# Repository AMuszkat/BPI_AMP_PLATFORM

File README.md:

# BPI AMP Platform

![How the platform is developed: a person sets the goal; an orchestrator agent plans the work and splits it between specialist agents working in parallel; every change is tested on two virtual speakers and reviewed, and a failed test or review sends it back to be fixed; a board operations agent deploys it to the real speakers and reports back](docs/images/agents.png)

The BPI AMP Platform is an autonomous, agentic platform for audio streaming, loudspeaker
tuning and digital signal processing (DSP). It is an open hardware and software stack for
building and tuning custom active loudspeakers, and its software is developed, tested and
deployed by a team of AI agents working under the direction of a person.

Each loudspeaker contains a BananaPi BPI-CM4 compute module on two purpose-built boards. The
speaker receives music over the network, applies its own tuning in real time, and drives a
woofer and a tweeter through two MAX98397 class-D amplifiers. Two speakers form a stereo pair,
tuned together from a single desktop application.

## Autonomous development

The platform is built by specialised AI agents, each responsible for one part of the stack:
the audio plugins, the speaker's audio engine, the controller application, the board
software, and the pictures of the project. A person sets the goal and approves the result. An
orchestrator agent plans the work, runs the specialists in parallel, merges their changes and
has a reviewer agent read them; a failed test or a review comment goes back to the agent that made the change. Every change is tested on two virtual speakers running on one
computer before it is published, and again by continuous integration. A board operations agent
installs the result on the real speakers and checks them. Safeguards apply throughout: no
private data enters the repository, nothing reaches the main branch without review, and a lab
lock keeps the agents away from the boards while they are on the bench. The agents, their
rules and their tools are described in [`CLAUDE.md`](CLAUDE.md) and
[`docs/autonomous-development.md`](docs/autonomous-development.md).

## Overview

Music is played as usual, from a computer or a phone; the speakers take care of the rest.

- **Network streaming.** Snapcast streams the music to both speakers in sync. AirPlay is also
  supported, through shairport-sync.
- **Processing in each speaker.** Each speaker processes its own channel. Its audio engine,
  `speakerd`, runs a chain of plugins: a correction filter, a crossover that divides the signal
  between the woofer and the tweeter, and a loudness contour. A speaker keeps playing from the
  settings stored on it, with no network or controller connected.
- **Tuning from a computer.** The controller application works like a familiar plugin host:
  plugins are added, connected and adjusted in their own editors, and both speakers follow
  within milliseconds. The settings are kept on the speakers, not in the application. The
  `ampd` service on the left speaker acts as the hub that keeps the pair in step; the right
  speaker applies what the hub sends. Level meters are read directly from each speaker.
- **Filters from measurements.** A set of Python tools measures each driver and designs the
  crossover and correction filters, which are then built into the plugins.

### Inside a speaker

Each speaker runs a layered stack: the platform's applications and PipeWire in user space,
the Linux audio drivers in the kernel, and the hardware beneath them.

The diagrams on this page are generated from [`docs/diagrams/`](docs/diagrams).

## Software modules

| Module | Purpose | Runs on | Location |
|---|---|---|---|
| Measurement and tuning tools | Measure a speaker's drivers, design its filters and export them for the plugins | the development computer (Python) | [`dsp/python_dsp_tools`](dsp/python_dsp_tools) |
| Audio plugins | `crossover`, `firConv` (correction), `loudness` and `ampScope`. The first three are each built in three variants from one source: **complete**, **control** (the editor only) and **headless** (the signal processing only) | the speakers (headless), the controller (control) | [`dsp/juce_plugins`](dsp/juce_plugins) |
| `speakerd` | The speaker's audio engine: hosts the plugin chain inside PipeWire, from the settings stored on the speaker | each speaker | [`dsp/juce_apps/speakerd`](dsp/juce_apps/speakerd) |
| `ampd` | The speaker's network service: stores and applies its settings; on the left speaker, also the hub of the pair | each speaker | [`firmware/ampd`](firmware/ampd) |
| Controller | The desktop application for tuning the pair through the hub | the listener's computer | [`dsp/juce_apps/controller`](dsp/juce_apps/controller) |
| PipeWire and Snapcast | The speaker's audio server, and the network stream that feeds it | each speaker | [`firmware/pipewire`](firmware/pipewire), [`firmware/snapcast-setup.sh`](firmware/snapcast-setup.sh) |
| Kernel support | Device tree, kernel configuration, and the amplifier and sound-card drivers | each speaker | [`firmware`](firmware) |
| Installers | `setup.sh` installs the audio software of a speaker, one component at a time | the development computer, or the speaker | [`firmware/setup.sh`](firmware/setup.sh) |

The controller, `ampd` and `speakerd` communicate through the protocol described in
[`docs/protocol.md`](docs/protocol.md). The overall design is described in
[`docs/remote-plugin-host.md`](docs/remote-plugin-host.md).

<table>
  <tr valign="top">
    <td width="50%"></td>
    <td width="50%"></td>
  </tr>
  <tr valign="top">
    <td><b>Tuning tool:</b> driver responses, the crossover sum and the corrected output, with every filter parameter adjustable live.</td>
    <td><b>The loudness plugin in the controller:</b> the plugin's own editor, acting as a remote control for both speakers.</td>
  </tr>
</table>

## Project status

The first three steps of the roadmap are complete and tested: the plugins in their three
variants, the `speakerd` audio engine, and the controller with the hub. Every test run checks
them against a pair of virtual speakers. On 1 November 2026 the platform was first installed
on a real board, which now starts `speakerd` at boot and plays the music Snapcast streams to it.
Running `ampd` and the controller on real boards is the next stage of that installation. Step 4
of the roadmap (oscilloscope data, a catalogue of the plugins on each speaker, and several
controllers at once) is next. `tools/roadmap.py` reports the current state.

## Hardware

The platform uses two boards joined by a board-to-board connector: a **base board** that
carries the BPI-CM4 module, with a USB-C port and a debug serial port, and a **speaker amp
board** with the two MAX98397 amplifiers, a boost converter for their supply and a 5 V
regulator for the rest of the system. The KiCad projects and their details are in
[`hardware/`](hardware/README.md).

The picture alternates between a render of the KiCad projects
([`hardware/render/`](hardware/README.md#renders)) and a photograph of the boards as built
([`all.jpeg`](all.jpeg)).

## Firmware

The board runs Armbian Linux with this repository's device tree, kernel configuration and
amplifier drivers, and PipeWire as its audio server. `firmware/setup.sh` installs the audio
software of a speaker, either from the development computer or on the board itself. The
bring-up procedure and the installers are described in [`firmware/`](firmware/README.md).

## Development

All development and testing, apart from work on the boards themselves, takes place on a Linux
x86_64 computer with no board attached. Only Podman and git are required: the builds and the
tests run in a development container with the same PipeWire version as the boards.

```sh
git clone --recurse-submodules https://github.com/AMuszkat/bpi_amp_platform
cd bpi_amp_platform
tools/test.sh all          # the complete test suite
tools/test.sh changed      # while working: the checks that cover the files changed
tools/build.sh loudness    # build one plugin or application into build/
tools/container.sh         # open a shell in the development container
```

The first run builds the container image and the JUCE framework, which takes a few minutes.
A focused check then takes between a few seconds and two minutes, and the complete suite about
two minutes. For a board, `tools/build.sh speakerd aarch64` cross-compiles into
`build/aarch64/`, and `firmware/setup.sh --mode target-remote` installs the result. Run
`tools/test.sh all` before installing on a board: nothing enforces it.

The Python measurement and tuning tools have their own quick start in
[`dsp/README.md`](dsp/README.md). The development process, including the test levels, the
development agents and continuous integration, is described in [`CLAUDE.md`](CLAUDE.md) and
[`docs/autonomous-development.md`](docs/autonomous-development.md).

## Repository layout

| Directory | Contents |
|---|---|
| [`hardware`](hardware/README.md) | KiCad projects: the base board and the amplifier board |
| [`firmware`](firmware/README.md) | Device tree, kernel configuration, amplifier drivers, PipeWire configuration, the installers and `ampd` |
| [`dsp`](dsp/README.md) | Measurement and tuning tools, the JUCE plugins, `speakerd`, the controller and the plugin test tool |
| [`docs`](docs) | The [system design](docs/remote-plugin-host.md), its [protocol](docs/protocol.md), the [block FIR filter](docs/p1-block-fir.md), the [development setup](docs/autonomous-development.md) and the [diagrams](docs/diagrams) |
| [`tests/vpair`](tests/vpair/README.md) | Two virtual speakers on one computer, for development and testing without boards |
| [`tools`](tools) | Build, test, container and board scripts |

## License

The software under [`dsp/`](dsp) is free software, licensed under the GNU Affero General Public
License v3.0; see [`dsp/LICENSE`](dsp/LICENSE).

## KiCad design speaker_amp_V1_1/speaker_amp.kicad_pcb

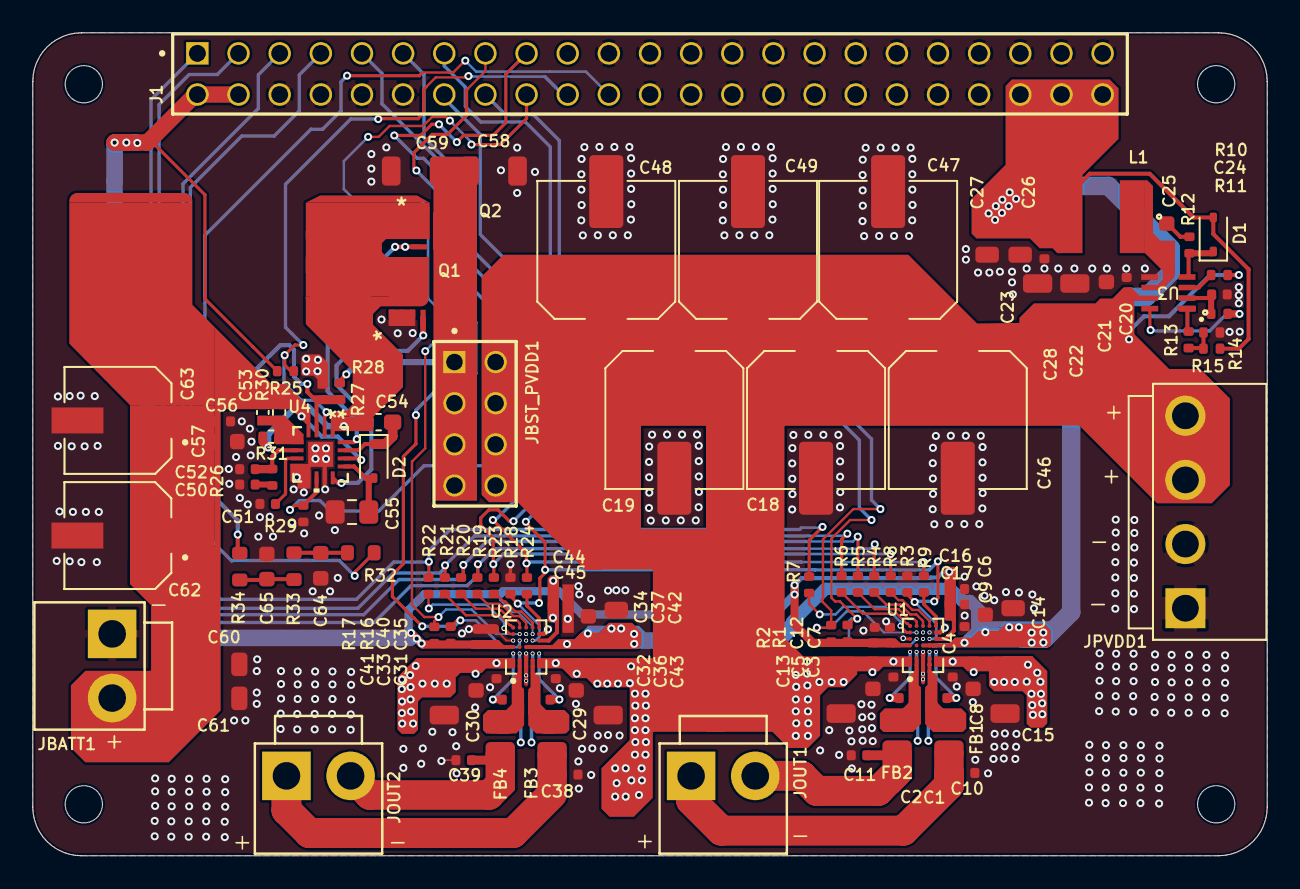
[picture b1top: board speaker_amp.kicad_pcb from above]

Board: 4 copper layers, 76.2 x 50.8 mm, 119 parts (0 on the bottom side), 65 nets.

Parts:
C1, C2, C3, C4, C6, C7, C16, C20, C24, C28, C29, C30, C31, C32, C34, C35, C44, C50, C51, C52, C56: 100nF; C_0402_1005Metric
C5, C8, C9, C21, C25, C33, C36, C37, C57, C64, C65: 1uF; C_0603_1608Metric
C10, C11, C38, C39: 150pF; C_0402_1005Metric
C12, C17, C40, C45: 1uF; C_0402_1005Metric
C13, C15, C22, C23, C41, C43, C58, C59: 10uF; C_1206_3216Metric
C14, C26, C27, C42: 22uF; C_0805_2012Metric
C18, C19, C46, C47, C48, C49: 470uF; C_ELEC_8x10
C53: 0.047uF; C_0402_1005Metric
C54: 1uF; C_0603_1608Metric_Pad1.08x0.95mm_HandSolder
C55: 4.7uF; C_0805_2012Metric_Pad1.18x1.45mm_HandSolder
C60, C61: 10uF; C_0805_2012Metric
C62, C63: 47uF; CAP_EEEFK1C470P
D1, D2: 1N4148WS; D_SOD-323
FB1, FB2, FB3, FB4: FERR_NFZ2MSD301SZ10L; NFZ2MSD301SZ10L
J1: CONN_2x23PIN; SAMTEC_SSW-123-01-T-D
JBATT1: Conn_01x02; B2P-VH
JBST_PVDD1: Conn_02x04_Odd_Even; TSW-104-07-F-D
JOUT1, JOUT2: Conn_01x02; B2P-VH
JPVDD1: Conn_01x04; B4P-VH
L1: L_74404054xx; IND_5040-WE-LQS_WRE
L2: 4.7uH; HCM1A1307-4R7-R
Q1, Q2: BSZ024N04LS6; PQFN330x330
R1, R3, R10, R11, R16, R18, R25, R26, R27, R28, R29: 10K; R_0402_1005Metric
R2, R12, R17: 4.7k; R_0402_1005Metric
R4, R5, R6, R7, R8, R9, R19, R20, R21, R22, R23, R24: 33r; R_0402_1005Metric
R13: 51K; R_0402_1005Metric
R14: 7.68K; R_0402_1005Metric
R15: 41.2K; R_0402_1005Metric
R30: 10M; R_0402_1005Metric
R31: 13.3K; R_0402_1005Metric
R32, R33, R34: R_0603_1608Metric
U1, U2: WLP35
U3: MP9943; QFN-8_MP9943_MNP
U4: LTC3786; QFN-16_UD_LIT

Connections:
+1V8: C7.1, C12.1, C16.1, C17.1, C35.1, C40.1, C44.1, C45.1, J1.2, J1.4, R1.1, R2.1, R16.1, R17.1, R25.1, U1.A4 (AVDD), U1.E5 (DVDD), U2.A4 (AVDD), U2.D6 (ADDR1), U2.E5 (DVDD)
+5V: C6.1, C9.1, C14.1, C26.1, C27.1, C28.1, C34.1, C37.1, C42.1, D1.2 (A), J1.42, J1.44, J1.46, L1.2, R15.1, U1.C4 (VBAT), U1.D4 (VBAT), U1.E4 (VBAT), U2.C4 (VBAT), U2.D4 (VBAT), U2.E4 (VBAT)
/Amp1/OUTN: C2.1, FB2.1, U1.B1 (OUTN), U1.B2 (OUTN)
/Amp1/OUTNSN: C11.1, FB2.2, JOUT1.2, U1.B3 (OUTNSNS)
/Amp1/OUTP: C1.2, FB1.1, U1.D1 (OUTP), U1.D2 (OUTP)
/Amp1/OUTPSN: C10.1, FB1.2, JOUT1.1, U1.D3 (OUTPSNS)
/Amp1/VBOOTN: C2.2, U1.A3 (VBOOTN)
/Amp1/VBOOTP: C1.1, U1.E3 (VBOOTP)
/Amp2/OUTN: C30.1, FB4.1, U2.B1 (OUTN), U2.B2 (OUTN)
/Amp2/OUTNSN: C39.1, FB4.2, JOUT2.2, U2.B3 (OUTNSNS)
/Amp2/OUTP: C29.2, FB3.1, U2.D1 (OUTP), U2.D2 (OUTP)
/Amp2/OUTPSN: C38.1, FB3.2, JOUT2.1, U2.D3 (OUTPSNS)
/Amp2/VBOOTN: C30.2, U2.A3 (VBOOTN)
/Amp2/VBOOTP: C29.1, U2.E3 (VBOOTP)
/Boost/OUT_FB: C58.1, C59.1, JBST_PVDD1.1, JBST_PVDD1.3, JBST_PVDD1.5, JBST_PVDD1.7, Q2.5 (D), R27.1
/Buck5V/PGOOD: R11.2, U3.8 (PG)
/GPIOA_1: J1.14, R3.1, R18.1, U1.D5 (/RESET), U2.D5 (/RESET)
/GPIOA_2: J1.13, R1.2, U1.B5 (IRQ)
/GPIOA_3: J1.16, R2.2, U1.B6 (LV_EN)
/GPIOA_4: J1.15, R16.2, U2.B5 (IRQ)
/GPIOA_5: J1.18, R17.2, U2.B6 (LV_EN)
/GPIOA_6: J1.17, R29.2, U4.10 (RUN)
/GPIOA_7: J1.20, R25.2, U4.2 (PGOOD)
/GPIOA_9: J1.22, R32.2
/I2C_EE_M2_SCL: J1.9, R9.1, R24.1
/I2C_EE_M2_SDA: J1.11, R8.1, R23.1
/ICC_AMP: U1.C6 (ICC), U2.C6 (ICC)
/TDMA_D0: J1.5, R6.1, R21.1
/TDMA_D1: J1.7, R7.1, R22.1
/TDMA_FS: J1.3, R5.1, R20.1
/TDMA_SCLK: J1.1, R4.1, R19.1
GND: C3.2, C4.2, C5.2, C6.2, C7.2, C8.2, C9.2, C10.2, C11.2, C12.2, C13.2, C14.2, C15.2, C16.2, C17.2, C18.2, C19.2, C20.2, C21.2, C22.2, C23.2, C24.2, C26.2, C27.2, C28.2, C31.2, C32.2, C33.2, C34.2, C35.2, C36.2, C37.2, C38.2, C39.2, C40.2, C41.2, C42.2, C43.2, C44.2, C45.2, C46.2, C47.2, C48.2, C49.2, C50.1, C51.1, C52.1, C55.2, C56.2, C57.2, C58.2, C59.2, C60.2, C61.2, C62.2, C63.2, C64.2, C65.2, J1.6, J1.8, J1.10, J1.12, J1.21, J1.23, J1.24, J1.25, J1.26, J1.27, J1.28, J1.29, J1.30, J1.31, J1.32, J1.33, J1.34, J1.35, J1.36, J1.37, J1.38, J1.39, J1.40, J1.41, J1.43, J1.45, JBATT1.1, JPVDD1.1, JPVDD1.2, Q1.1 (S), Q1.2 (S), Q1.3 (S), R3.2, R14.2, R18.2, R28.2, R29.1, U1.A5 (AGND), U1.C1 (PGND), U1.C2 (PGND), U1.C3 (PGND), U1.C5 (ADDR2), U1.D6 (ADDR1), U1.E6 (DGND), U2.A5 (AGND), U2.C1 (PGND), U2.C2 (PGND), U2.C3 (PGND), U2.C5 (ADDR2), U2.E6 (DGND), U3.5 (GND), U4.8 (PLLIN/MODE), U4.9 (FREQ), U4.11 (GND), U4.17 (EPAD)
unnamed: C25.1, R12.2
unnamed: C50.2, R26.2
unnamed: C64.1, R32.1, R33.2
unnamed: C65.1, R33.1, R34.2
unnamed: D1.1 (K), R12.1, U3.4 (BST)
unnamed: C55.1, D2.2 (A), U4.13 (INTVCC)
unnamed: C54.2, D2.1 (K), U4.15 (BOOST)
unnamed: C54.1, L2.2, Q1.5 (D), Q2.1 (S), Q2.2 (S), Q2.3 (S), R31.2, U4.1 (SW)
unnamed: Q1.4 (G), U4.12 (BG)
unnamed: Q2.4 (G), U4.16 (TG)
unnamed: R13.1, R14.1, R15.2
unnamed: R4.2, U1.C7 (BCLK)
unnamed: R6.2, U1.A7 (DIN)
unnamed: R7.2, U1.A6 (DOUT)
unnamed: R5.2, U1.B7 (LRCLK)
unnamed: R9.2, U1.E7 (SCL)
unnamed: R8.2, U1.D7 (SDA)
unnamed: R19.2, U2.C7 (BCLK)
unnamed: R21.2, U2.A7 (DIN)
unnamed: R22.2, U2.A6 (DOUT)
unnamed: R20.2, U2.B7 (LRCLK)
unnamed: R24.2, U2.E7 (SCL)
unnamed: R23.2, U2.D7 (SDA)
unnamed: R10.2, U3.3 (EN/SYNC)
unnamed: R13.2, U3.1 (FB)
unnamed: C25.2, L1.1, U3.6 (SW)
unnamed: C24.1, R11.1, U3.2 (VCC)
unnamed: C52.2, R26.1, U4.6 (ITH)
unnamed: C53.2, R30.2, R31.1, U4.5 (SENSE-)
unnamed: C51.2, U4.7 (SS)
unnamed: R27.2, R28.1, R34.1, U4.3 (VFB)
PVDD: C3.1, C4.1, C5.1, C8.1, C13.1, C15.1, C18.1, C19.1, C20.1, C21.1, C22.1, C23.1, C31.1, C32.1, C33.1, C36.1, C41.1, C43.1, C46.1, C47.1, C48.1, C49.1, JBST_PVDD1.2, JBST_PVDD1.4, JBST_PVDD1.6, JBST_PVDD1.8, JPVDD1.3, JPVDD1.4, R10.1, U1.A1 (PVDD), U1.A2 (PVDD), U1.E1 (PVDD), U1.E2 (PVDD), U2.A1 (PVDD), U2.A2 (PVDD), U2.E1 (PVDD), U2.E2 (PVDD), U3.7 (IN)
VBATT_EXT: C53.1, C56.1, C57.1, C60.1, C61.1, C62.1, C63.1, JBATT1.2, L2.1, R30.1, U4.4 (SENSE+), U4.14 (VBIAS)

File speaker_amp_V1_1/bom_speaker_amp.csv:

Reference;Description;Value;Qty;Type;Voltage;Footprint size;Tolerance;DNP;MPN;Manufacturer;Critical part (must be same as MPN)
D1,D2;DIODE;1N4148WS;2;;;;;;1N4148WS-E3-18;Vishay Semiconductors;
U4;IC;LTC3786;1;;;;;;LTC3786EUD#TRPBF;Analog Devices;Critical
U3;IC;MP9943;1;;;;;;MP9943AGQ-Z;Monolithic Power Systems (MPS);Critical
U1,U2;;MAX98397;2;;;;;;MAX98397EWB+T;Analog Devices;Critical
R31;RES;13.3K;1;;;0402;1%;;RMCF0402FT13K3;SEI Stackpole;
R30;RES;10M;1;;;0402;1%;;RMCF0402FT10M0;SEI Stackpole;
R15;RES;41.2K;1;;;0402;1%;;RC0402FR-1341K2L;YAGEO;
R14;RES;7.68K;1;;;0402;1%;;RC0402FR-077K68L;YAGEO;
R13;RES;51K;1;;;0402;1%;;RC0402FR-0751KP;YAGEO;
R12;Resistor;4.7k;1;;;0603;1%;;CRCW06034K70FKEC;Vishay / Dale;
R4,R5,R6,R7,R8,R9,R19,R20,R21,R22,R23,R24;RES;33r;12;;;0402;1%;;RC0402FR-1333RL;YAGEO;
R2,R17;RES;4.7k;2;;;0402;1%;;AC0402FR-134K7L;YAGEO;
R1,R3,R10,R11,R16,R18,R25,R26,R27,R28,R29;RES;10K;11;;;0402;1%;;AC0402FR-0710KL;YAGEO;
Q1,Q2;100A Id, 60V Vds, OptiMOS N-Channel Power MOSFET, 2.8mOhm Ron, Qg (typ) 31.0nC, PG-TDSON-8;BSZ024N04LS6;2;;;;;;BSZ024N04LS6;Infineon;Critical
L2;IND;4.7uH;1;;;;;;HCM1A1307-4R7-R;Bussmann / Eaton;Critical
L1;Inductor;10uH;1;;;;;;74404054100;Würth Elektronik;Critical
JPVDD1;CONN;Conn_01x04;1;;;;;DNP;B4P-VH;JST Sales America Inc.;
JBST_PVDD1;HEADER;Conn_02x04_Odd_Even;1;;;;;DNP;TSW-104-07-F-D;Samtec;
JBATT1,JOUT1,JOUT2;CONN;Conn_01x02;3;;;;;DNP;B2P-VH;JST Sales America Inc.;
FB1,FB2,FB3,FB4;FERR;FERR_NFZ2MSD301SZ10L;4;;;0806;;;NFZ2MSD301SZ10L;Murata;Critical
C64,C65,J1,R32,R33,R34;-;-;-;-;-;-;-;DNP;;;
C62,C63;CAP;47uF;2;ELEC;16V;-;10%;DNP;EEE-FK1C470P;Panasonic;
C60,C61;CAP;10uF;2;X7R;25V;0805;20%;;CL21B106KAYQNNE;Samsung Electro-Mechanics;
C55;CAP;4.7uF;1;X7R;25V;0805;10%;;GRM21BZ71E475KE15L;Murata;
C54;CAP;1uF;1;X7R;50V;0603;10%;;GCM188R71E104KA57D;Murata;
C53;CAP;0.047uF;1;X7R;25V;0402;5%;;GRM155R71E473JA88D;Murata;
C18,C19,C46,C47,C48,C49;;470uF;6;ELEC;50V;-;10%;DNP;EMZS350ARA471MHA0G;Chemi-Con;
C14,C26,C27,C42;CAP;22uF;4;X7R;10V;0805;20%;;GRM21BZ71A226ME15K;Murata;
C13,C15,C22,C23,C41,C43,C58,C59;CAP;10uF;8;X7R;50V;1206;10%;;CL31B106KBHNNNE;Samsung Electro-Mechanics;
C12,C17,C40,C45;CAP;1uF;4;X7R;10V;0402;10%;;GRM155Z71A105KE01J;Murata;Critical
C10,C11,C38,C39;CAP;150pF;4;NP0;50V;0402;10%;;UMK105CG151JVHF;TAIYO YUDEN;
C5,C8,C9,C21,C25,C33,C36,C37,C57;CAP;1uF;9;X7R;50V;0603;10%;;CL10B105KB8NQNC;Samsung Electro-Mechanics;
C1,C2,C3,C4,C6,C7,C16,C20,C24,C28,C29,C30,C31,C32,C34,C35,C44,C50,C51,C52,C56;CAP;100nF;21;X7R;50V;0402;10%;;GRM155R71H104KE14D;Murata;

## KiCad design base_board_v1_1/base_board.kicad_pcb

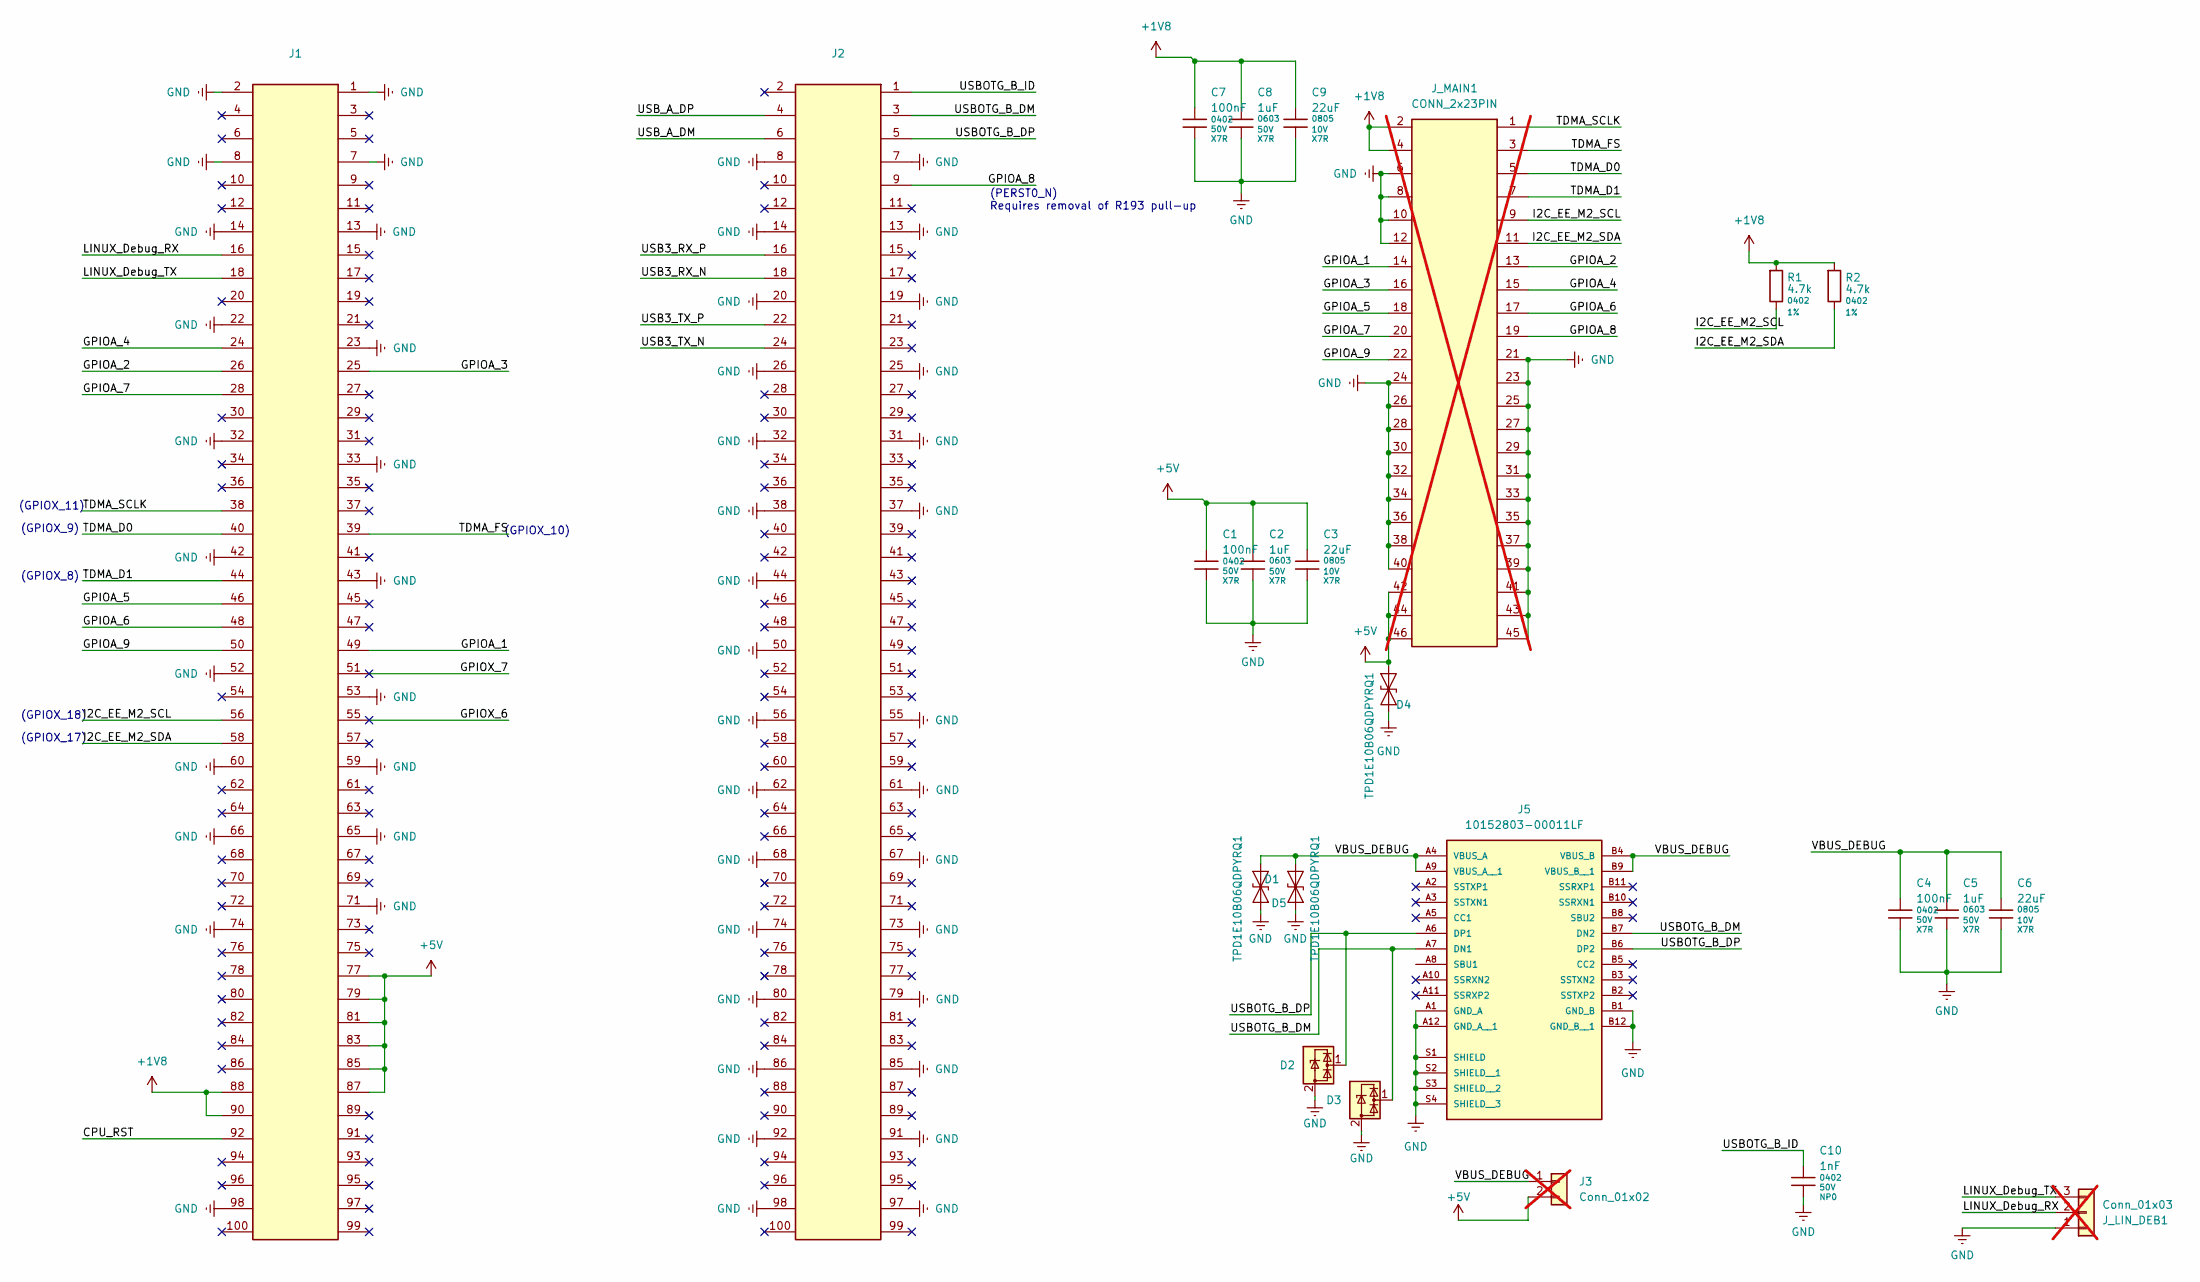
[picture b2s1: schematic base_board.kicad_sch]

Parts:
C1, C4, C7: 100nF; C_0402_1005Metric; Voltage 50V; Tolerance 10%; MPN GRM155R71H104KE14D
C2, C5, C8: 1uF; C_0603_1608Metric; Voltage 50V; Tolerance 10%; MPN CL10B105KB8NQNC
C3, C6, C9: 22uF; C_0805_2012Metric; Voltage 10V; Tolerance 20%; MPN GRM21BZ71A226ME15K
C10: 1nF; C_0402_1005Metric; Voltage 50V; Tolerance 5%; MPN C0402C102J5GAC
D1, D4, D5: SOD-523; MPN TPD1E10B06QDPYRQ1
D2, D3: Texas_DPY0002A_0.6x1mm_P0.65mm; MPN TPD1E1B04
J1: CONN_DF40HC-100DS_HIR_v1_1; MPN DF40HC(3.0)-100DS-0.4V(51
J2: CONN_DF40HC-100DS_HIR_v1_1; MPN DF40HC(3.0)-100DS-0.4V(51
J3: Conn_01x02; PinHeader_2x01_P2.54mm_Vertical; not fitted
J5: 10152803-00011LF; AMPHENOL_10152803-00011LF; PARTREV A
J_LIN_DEB1: Conn_01x03; PinHeader_1x03_P2.54mm_Vertical; not fitted
J_MAIN1: CONN_2x23PIN; SAMTEC_SSW-123-01-T-D; not fitted
R1, R2: 4.7k; R_0402_1005Metric; Tolerance 1%; MPN RCG04024K70FKED

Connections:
+1V8: C7.1, C8.1, C9.1, J1.88, J1.90, J_MAIN1.2, J_MAIN1.4, R1.1, R2.1
+5V: C1.1, C2.1, C3.1, D4.1 (A1), J1.77, J1.79, J1.81, J1.83, J1.85, J1.87, J3.2, J_MAIN1.42, J_MAIN1.44, J_MAIN1.46
/CPU_RST: J1.92
/GPIOA_1: J1.49, J_MAIN1.14
/GPIOA_2: J1.26, J_MAIN1.13
/GPIOA_3: J1.25, J_MAIN1.16
/GPIOA_4: J1.24, J_MAIN1.15
/GPIOA_5: J1.46, J_MAIN1.18
/GPIOA_6: J1.48, J_MAIN1.17
/GPIOA_7: J1.28, J_MAIN1.20
/GPIOA_8: J2.9, J_MAIN1.19
/GPIOA_9: J1.50, J_MAIN1.22
/GPIOX_6: J1.55
/GPIOX_7: J1.51
/I2C_EE_M2_SCL: J1.56, J_MAIN1.9, R1.2
/I2C_EE_M2_SDA: J1.58, J_MAIN1.11, R2.2
/LINUX_Debug_RX: J1.16, J_LIN_DEB1.2
/LINUX_Debug_TX: J1.18, J_LIN_DEB1.3
/TDMA_D0: J1.40, J_MAIN1.5
/TDMA_D1: J1.44, J_MAIN1.7
/TDMA_FS: J1.39, J_MAIN1.3
/TDMA_SCLK: J1.38, J_MAIN1.1
/USB3_RX_N: J2.18
/USB3_RX_P: J2.16
/USB3_TX_N: J2.24
/USB3_TX_P: J2.22
/USBOTG_B_DM: D3.1 (I/O), J2.3, J5.A7 (DN1), J5.B7 (DN2)
/USBOTG_B_DP: D2.1 (I/O), J2.5, J5.A6 (DP1), J5.B6 (DP2)
/USBOTG_B_ID: C10.1, J2.1
/USB_A_DM: J2.6
/USB_A_DP: J2.4
/VBUS_DEBUG: C4.1, C5.1, C6.1, D1.1 (A1), D5.1 (A1), J3.1, J5.A4 (VBUS_A), J5.A9 (VBUS_A__1), J5.B4 (VBUS_B), J5.B9 (VBUS_B__1)
GND: C1.2, C2.2, C3.2, C4.2, C5.2, C6.2, C7.2, C8.2, C9.2, C10.2, D1.2 (A2), D2.2 (GND), D3.2 (GND), D4.2 (A2), D5.2 (A2), J1.1, J1.2, J1.7, J1.8, J1.13, J1.14, J1.22, J1.23, J1.32, J1.33, J1.42, J1.43, J1.52, J1.53, J1.59, J1.60, J1.65, J1.66, J1.71, J1.74, J1.98, J2.7, J2.8, J2.13, J2.14, J2.19, J2.20, J2.25, J2.26, J2.31, J2.32, J2.37, J2.38, J2.44, J2.50, J2.55, J2.56, J2.61, J2.62, J2.67, J2.68, J2.73, J2.74, J2.79, J2.80, J2.85, J2.86, J2.91, J2.92, J2.97, J2.98, J5.A1 (GND_A), J5.A12 (GND_A__1), J5.B1 (GND_B), J5.B12 (GND_B__1), J5.S1 (SHIELD), J5.S2 (SHIELD__1), J5.S3 (SHIELD__2), J5.S4 (SHIELD__3), J_LIN_DEB1.1, J_MAIN1.6, J_MAIN1.8, J_MAIN1.10, J_MAIN1.12, J_MAIN1.21, J_MAIN1.23, J_MAIN1.24, J_MAIN1.25, J_MAIN1.26, J_MAIN1.27, J_MAIN1.28, J_MAIN1.29, J_MAIN1.30, J_MAIN1.31, J_MAIN1.32, J_MAIN1.33, J_MAIN1.34, J_MAIN1.35, J_MAIN1.36, J_MAIN1.37, J_MAIN1.38, J_MAIN1.39, J_MAIN1.40, J_MAIN1.41, J_MAIN1.43, J_MAIN1.45

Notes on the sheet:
(GPIOX_8)
(GPIOX_9)
(GPIOX_18)
(GPIOX_17)
(GPIOX_11)
(GPIOX_10)
(PERST0_N) Requires removal of R193 pull-up

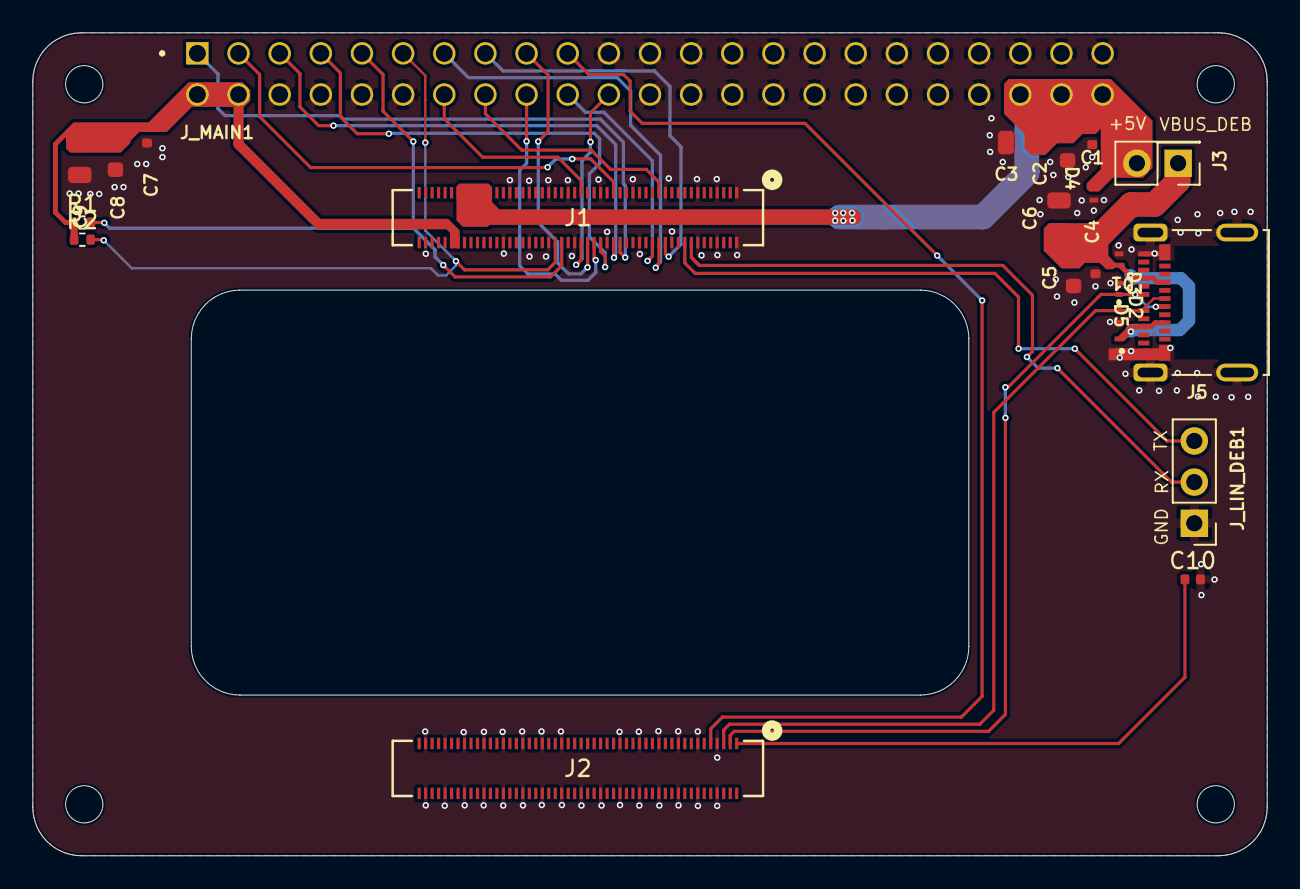
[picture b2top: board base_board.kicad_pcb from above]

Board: 2 copper layers, 76.2 x 50.8 mm, 23 parts (0 on the bottom side), 24 nets.

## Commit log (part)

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2025-10-24 Add initial files
2025-10-24 Add md pic
2025-10-24 Change file name
2025-10-25 Change project folder names
2025-10-25 Cleaning
2025-10-25 Add coming soon...
